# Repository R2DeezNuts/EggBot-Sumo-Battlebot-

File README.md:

# Proxecto Battlebot · Equipo Eggbots

Este repositorio reúne o deseño, o software e a documentación do noso BattleBot. A [web de Eggbots](https://battlebots.robotica.gal/Eggbots/) recolle a documentación completa do proxecto.

## Equipo
O equipo está formado por:
- **Enrique Comesaña Figueroa**: Coordinador e responsable do deseño de hardware e da construción.
- **Juan José Prado Neira**: Responsable do deseño e da implementación do software.
- **Marcos Fernández González**: Responsable da web e da documentación.
- **Javier Rego Bargos**: Responsable do deseño mecánico e electrónico.

## Estrutura do repositorio

O repositorio organízase en:
- ***README.md***: Este ficheiro.
- ***web***: Código fonte da web do proxecto.
- ***electronica***: Deseño dos circuítos de control e das placas.
- ***mecanica***: Deseño da estrutura do robot e planos de fabricación.
- ***software***: Software do robot.
- ***.gitlab-ci.yml***: Proceso de publicación da web.

## Compoñentes

Consulta a [lista de compoñentes](https://docs.google.com/spreadsheets/d/1ZMKZPNqryC1lRq46kaxvph4U0cHYfyVd0BvwiHCcG7o/edit?usp=sharing) para ver o material empregado.

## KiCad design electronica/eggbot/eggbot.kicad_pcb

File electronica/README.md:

# Deseño electrónico do robot
Nesta carpeta incluense os deseños e materiais electricos/electronicos necesarios para a construcción do robot.

A carpeta ten a seguinte estructura:
- ...
- ...

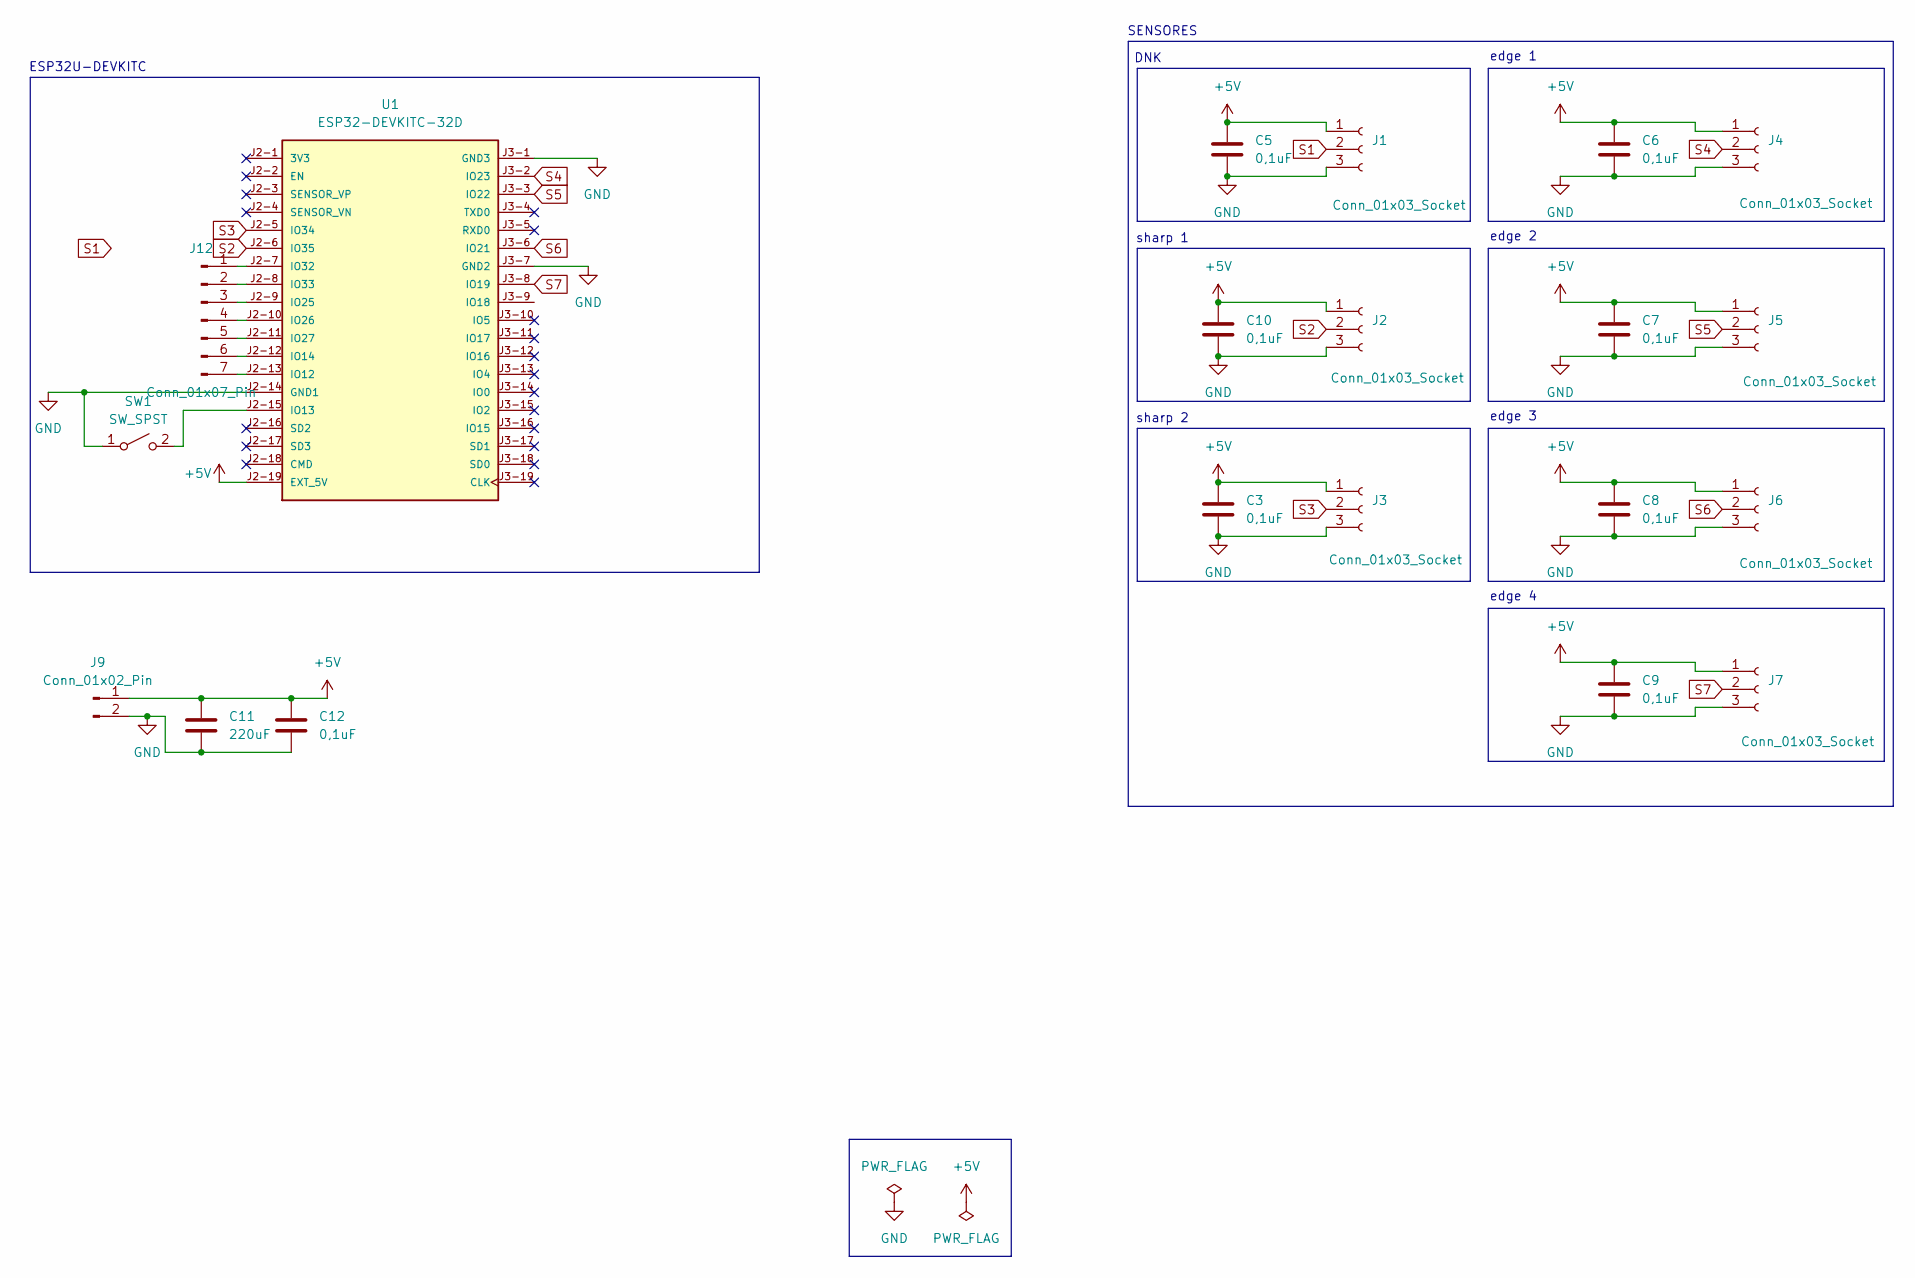
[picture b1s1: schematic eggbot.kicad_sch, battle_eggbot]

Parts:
C3, C5, C6, C7, C8, C9, C10, C12: 0,1uF; C_Disc_D4.3mm_W1.9mm_P5.00mm
C11: 220uF; CP_Radial_D4.0mm_P2.00mm
J1, J2, J3, J4, J5, J6, J7: Conn_01x03_Socket; pad_sensores_v2
J9: Conn_01x02_Pin; pad_salida_UBEC
J12: Conn_01x07_Pin; pad_7
SW1: SW_SPST; pad_2_èq
U1: ESP32-DEVKITC-32D; MODULE_ESP32-DEVKITC-32D; PARTREV V4

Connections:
+5V: C3.2, C5.2, C6.2, C7.2, C8.2, C9.2, C10.2, C11.2, C12.2, J1.1, J2.1, J3.1, J4.1, J5.1, J6.1, J7.1, J9.1, U1.J2-19 (EXT_5V)
GND: C3.1, C5.1, C6.1, C7.1, C8.1, C9.1, C10.1, C11.1, C12.1, J1.3, J2.3, J3.3, J4.3, J5.3, J6.3, J7.3, J9.2, SW1.1 (A), U1.J2-14 (GND1), U1.J3-1 (GND3), U1.J3-7 (GND2)
unnamed: J12.1, U1.J2-7 (IO32)
unnamed: J12.2, U1.J2-8 (IO33)
unnamed: J12.3, U1.J2-9 (IO25)
unnamed: J12.4, U1.J2-10 (IO26)
unnamed: J12.5, U1.J2-11 (IO27)
unnamed: J12.6, U1.J2-12 (IO14)
unnamed: J12.7, U1.J2-13 (IO12)
unnamed: SW1.2 (B), U1.J2-15 (IO13)
S1: J1.2, U1.J3-9 (IO18)
S2: J2.2, U1.J2-6 (IO35)
S3: J3.2, U1.J2-5 (IO34)
S4: J4.2, U1.J3-2 (IO23)
S5: J5.2, U1.J3-3 (IO22)
S6: J6.2, U1.J3-6 (IO21)
S7: J7.2, U1.J3-8 (IO19)

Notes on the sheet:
sharp 1
edge 3
DNK
ESP32U-DEVKITC
SENSORES
edge 4
edge 1
sharp 2
edge 2

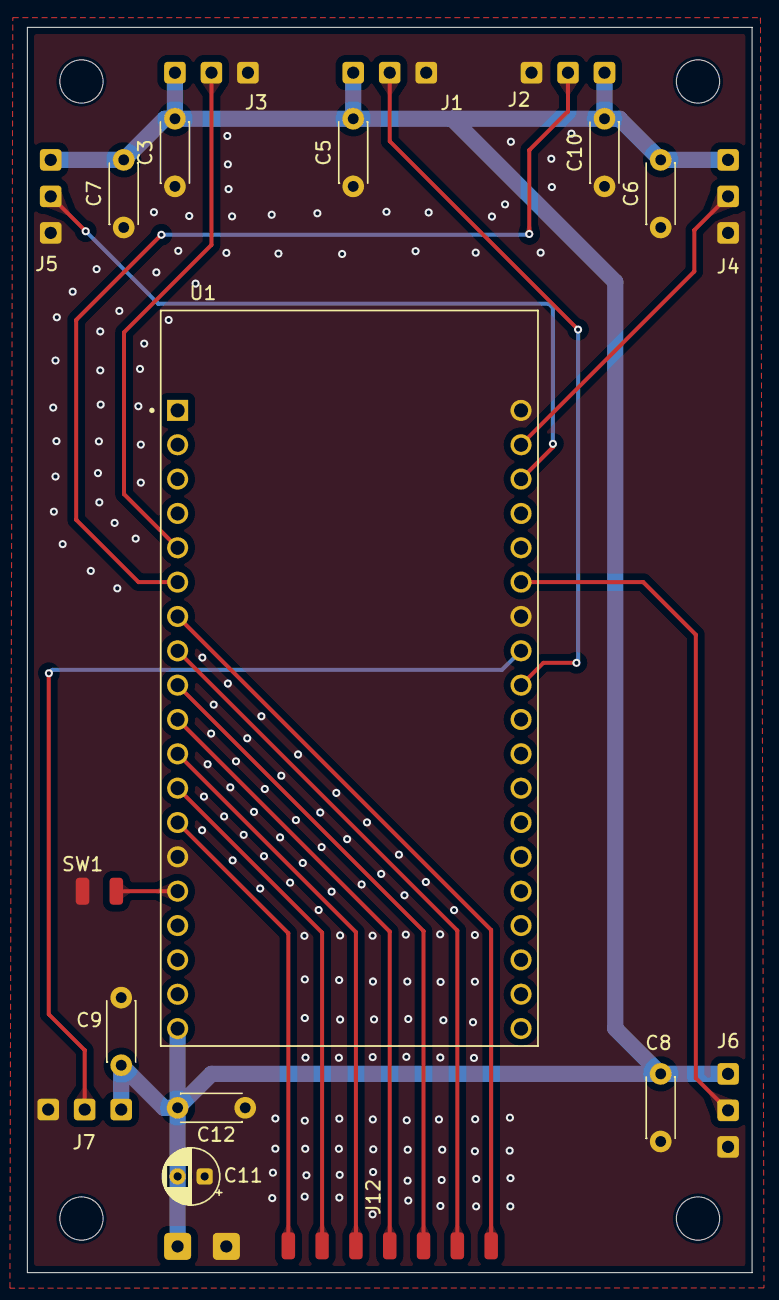
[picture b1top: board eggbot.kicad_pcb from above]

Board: 2 copper layers, 53.6 x 92.1 mm, 24 parts (0 on the bottom side), 17 nets.

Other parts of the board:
H0, H1, H3, H4: MountingHole_3.2mm_M3
